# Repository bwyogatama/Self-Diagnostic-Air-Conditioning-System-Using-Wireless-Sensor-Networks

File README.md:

# Self-Diagnostic-Air-Conditioning-System-Using-Wireless-Sensor-Networks

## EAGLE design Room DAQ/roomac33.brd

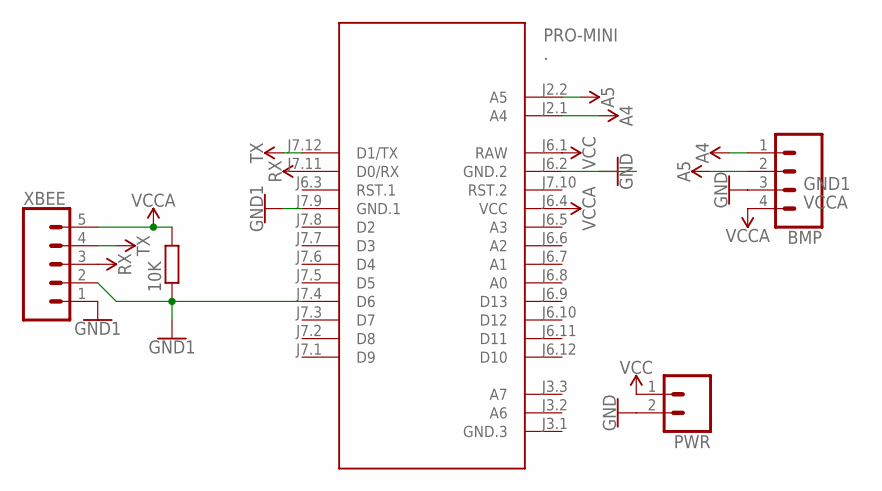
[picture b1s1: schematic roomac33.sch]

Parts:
10K: R0204/7; 0204/7
BMP: CONN_04; 1X04
PRO-MINI: .; ARDUINO-PRO-MINI#NP
PWR: CONN_025MM; SCREWTERMINAL-5MM-2
XBEE: CONN_05; 1X05

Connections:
A4: BMP.1, PRO-MINI.J2.1 (A4)
A5: BMP.2, PRO-MINI.J2.2 (A5)
GND: 10K.1, PRO-MINI.J7.4 (D6), PRO-MINI.J7.9 (GND.1), XBEE.1, XBEE.2
GND1: BMP.3, PRO-MINI.J6.2 (GND.2), PWR.2
RX: PRO-MINI.J7.11 (D0/RX), XBEE.3
TX: PRO-MINI.J7.12 (D1/TX), XBEE.4
VCC: PRO-MINI.J6.1 (RAW), PWR.1
VCCA: 10K.2, BMP.4, PRO-MINI.J6.4 (VCC), XBEE.5

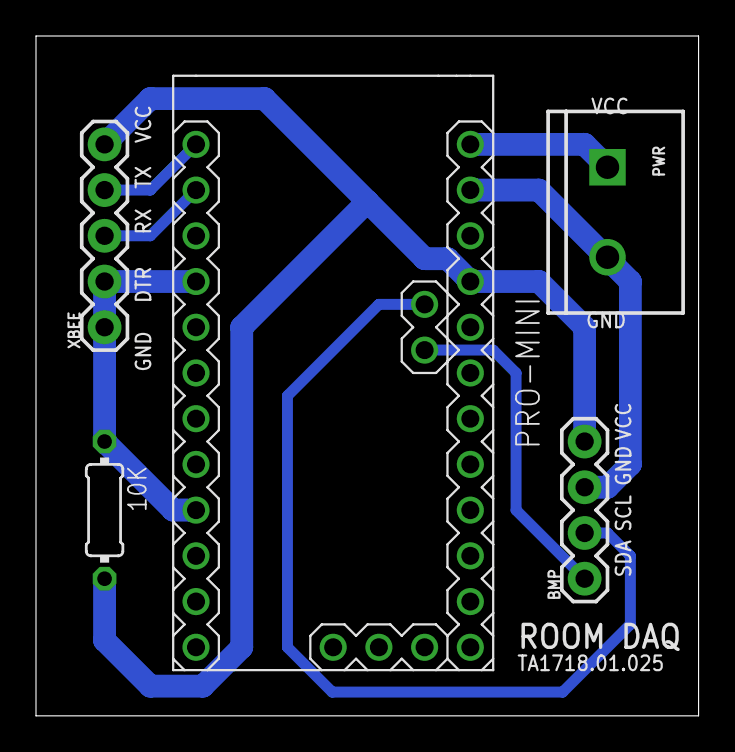
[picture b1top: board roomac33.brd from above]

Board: 2 copper layers, 36.8 x 37.8 mm, 5 parts (0 on the bottom side), 8 nets.

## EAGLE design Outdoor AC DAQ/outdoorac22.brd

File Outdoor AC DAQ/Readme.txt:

Arduino Code for Outdoor AC DAQ

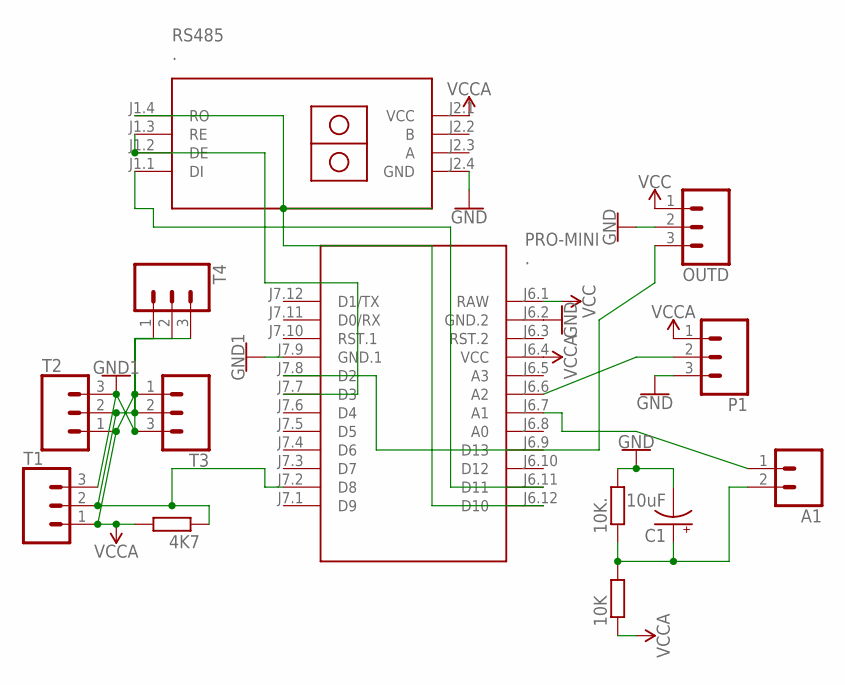
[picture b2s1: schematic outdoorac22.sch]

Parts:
4K7, 10K, 10K.: R0204/7; 0204/7
A1: CONN_02; 1X02
C1: 10uF; CPOL-RADIAL-2.5MM-5MM
OUTD: CONN_03-SCREW-5MM; SCREWTERMINAL-5MM-3
P1: CONN_03; 1X03
PRO-MINI: .; ARDUINO-PRO-MINI#SMP
RS485: .; RS485-TTL-CONVERTER
T1, T2, T3, T4: CONN_03; 1X03

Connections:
GND: PRO-MINI.J7.9 (GND.1), T1.3, T2.3, T3.3, T4.3
GND1: 10K..2, C1.2 (-), OUTD.2, P1.3, PRO-MINI.J6.2 (GND.2), RS485.J2.4 (GND)
unnamed: 4K7.1, PRO-MINI.J7.2 (D8), T1.2, T2.2, T3.2, T4.2
unnamed: A1.1, PRO-MINI.J6.7 (A1)
unnamed: P1.2, PRO-MINI.J6.6 (A2)
unnamed: 10K.2, 10K..1, A1.2, C1.1 (+)
unnamed: PRO-MINI.J7.7 (D3), RS485.J1.2 (DE), RS485.J1.3 (RE)
unnamed: OUTD.3, PRO-MINI.J7.8 (D2)
unnamed: PRO-MINI.J6.11 (D11), RS485.J1.1 (DI)
unnamed: PRO-MINI.J6.12 (D10), RS485.J1.4 (RO)
VCC: OUTD.1, PRO-MINI.J6.1 (RAW)
VCCA: 4K7.2, 10K.1, P1.1, PRO-MINI.J6.4 (VCC), RS485.J2.1 (VCC), T1.1, T2.1, T3.1, T4.1

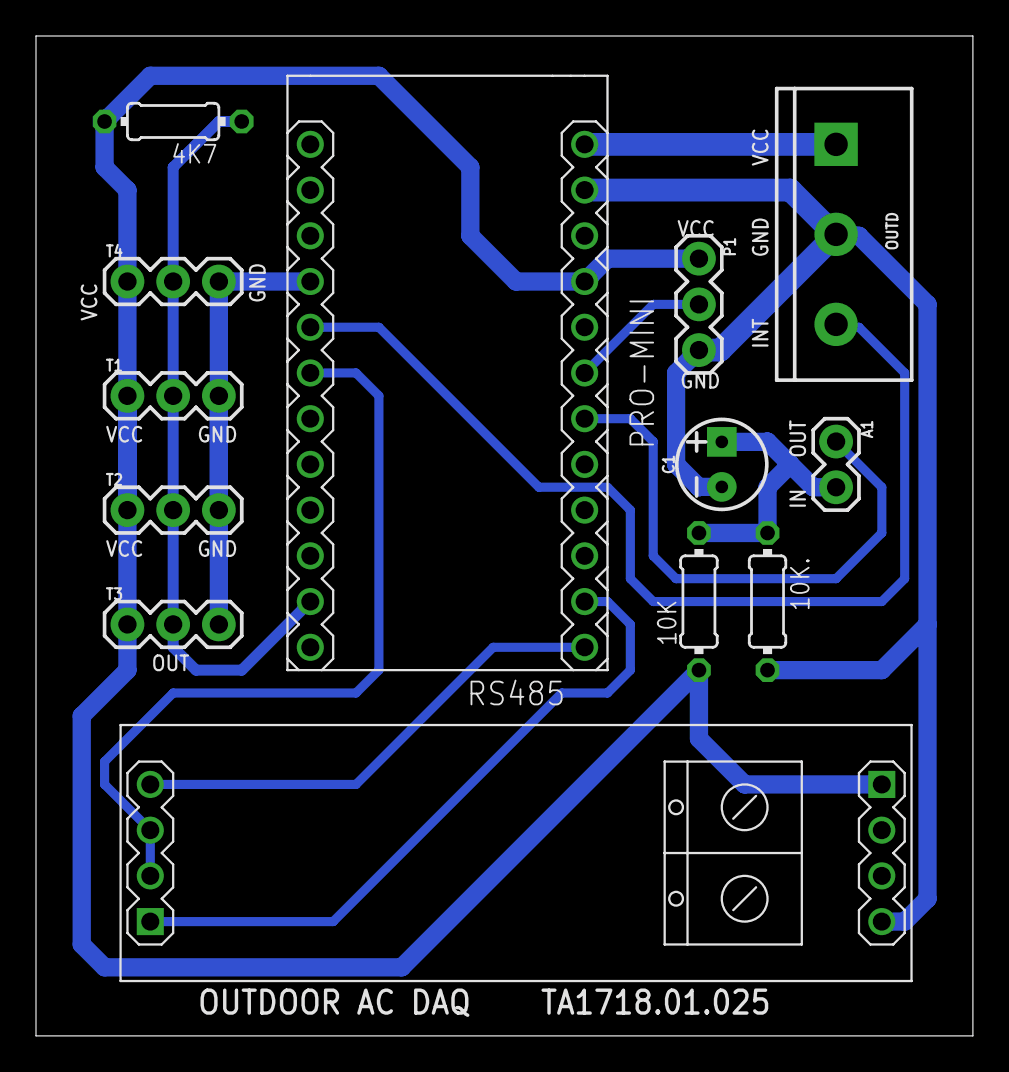
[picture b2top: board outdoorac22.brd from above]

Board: 2 copper layers, 52.0 x 55.5 mm, 13 parts (0 on the bottom side), 12 nets.

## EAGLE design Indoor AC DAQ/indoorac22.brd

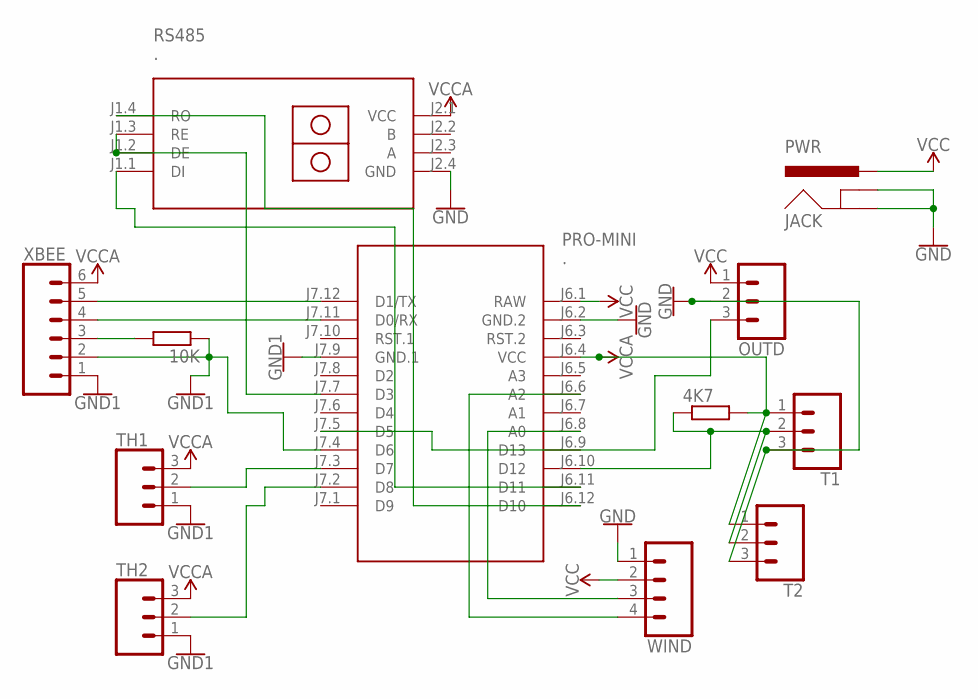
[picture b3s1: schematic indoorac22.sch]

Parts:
4K7, 10K: R0204/7; 0204/7
JACK: PWR; POWER_JACK_PTH_LOCK
OUTD: CONN_03-SCREW-5MM; SCREWTERMINAL-5MM-3
PRO-MINI: .; ARDUINO-PRO-MINI#SMP
RS485: .; RS485-TTL-CONVERTER
T1, T2: CONN_03; 1X03
TH1, TH2: CONN_03; 1X03
WIND: CONN_04; 1X04
XBEE: CONN_06SILK_FEMALE_PTH; 1X06

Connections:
GND: 10K.1, PRO-MINI.J7.4 (D6), PRO-MINI.J7.9 (GND.1), TH1.1, TH2.1, XBEE.1, XBEE.2
GND1: JACK.GND, JACK.GNDBREAK, OUTD.2, PRO-MINI.J6.2 (GND.2), RS485.J2.4 (GND), T1.3, T2.3, WIND.1
unnamed: 4K7.1, PRO-MINI.J6.10 (D12), T1.2, T2.2
unnamed: PRO-MINI.J6.8 (A0), WIND.3
unnamed: 10K.2, XBEE.3
unnamed: PRO-MINI.J6.6 (A2), WIND.4
unnamed: PRO-MINI.J7.7 (D3), RS485.J1.2 (DE), RS485.J1.3 (RE)
unnamed: OUTD.3, PRO-MINI.J7.5 (D5)
unnamed: PRO-MINI.J6.11 (D11), RS485.J1.1 (DI)
unnamed: PRO-MINI.J6.12 (D10), RS485.J1.4 (RO)
unnamed: PRO-MINI.J7.12 (D1/TX), XBEE.5
unnamed: PRO-MINI.J7.11 (D0/RX), XBEE.4
unnamed: PRO-MINI.J7.3 (D7), TH1.2
unnamed: PRO-MINI.J7.2 (D8), TH2.2
VCC: JACK.PWR, OUTD.1, PRO-MINI.J6.1 (RAW), WIND.2
VCCA: 4K7.2, PRO-MINI.J6.4 (VCC), RS485.J2.1 (VCC), T1.1, T2.1, TH1.3, TH2.3, XBEE.6

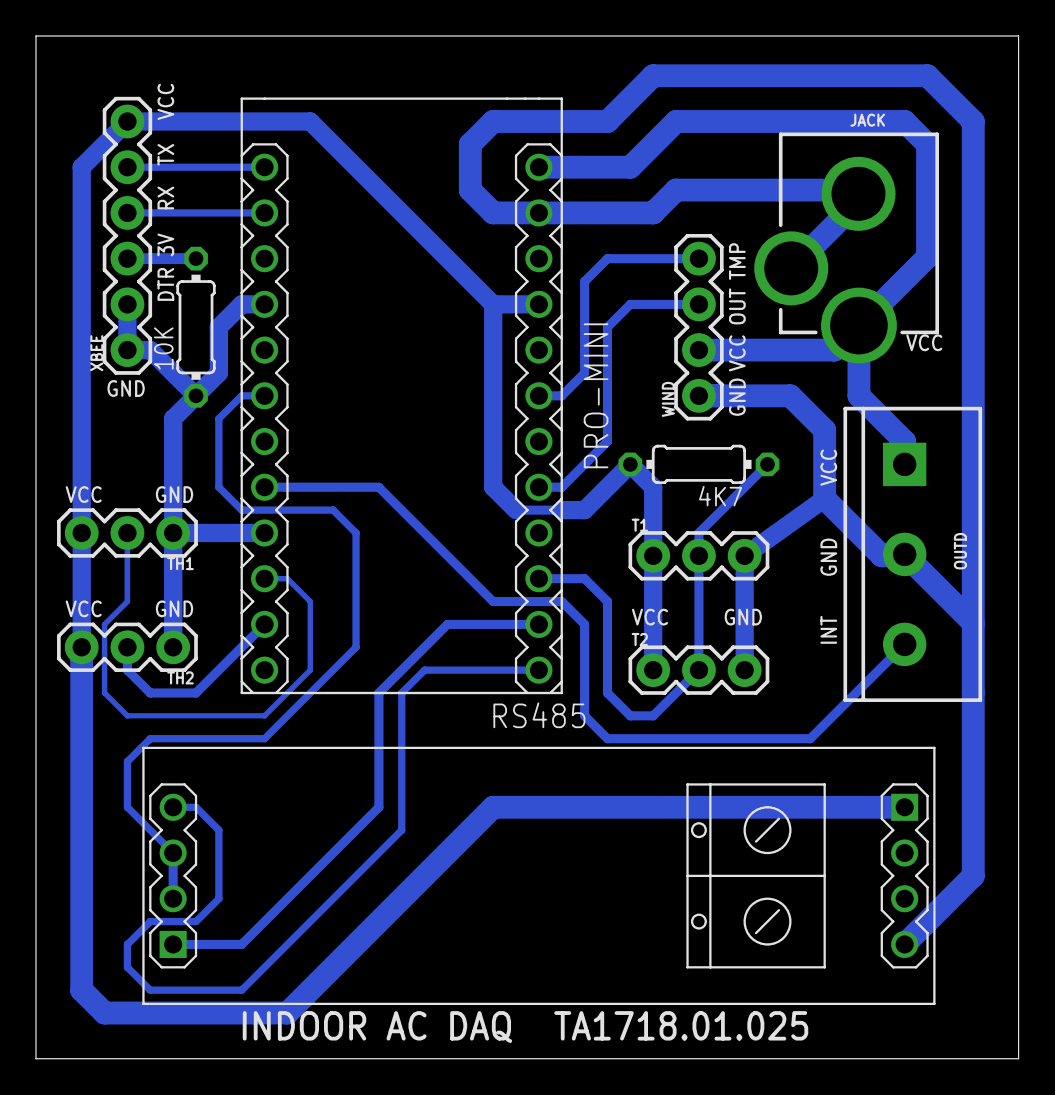
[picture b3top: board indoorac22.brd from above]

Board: 2 copper layers, 54.6 x 56.8 mm, 12 parts (0 on the bottom side), 16 nets.

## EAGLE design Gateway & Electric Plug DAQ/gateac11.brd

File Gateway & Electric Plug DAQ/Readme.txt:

Raspberry Pi Python Code for Gateway
Arduino Code for Electric Plug DAQ

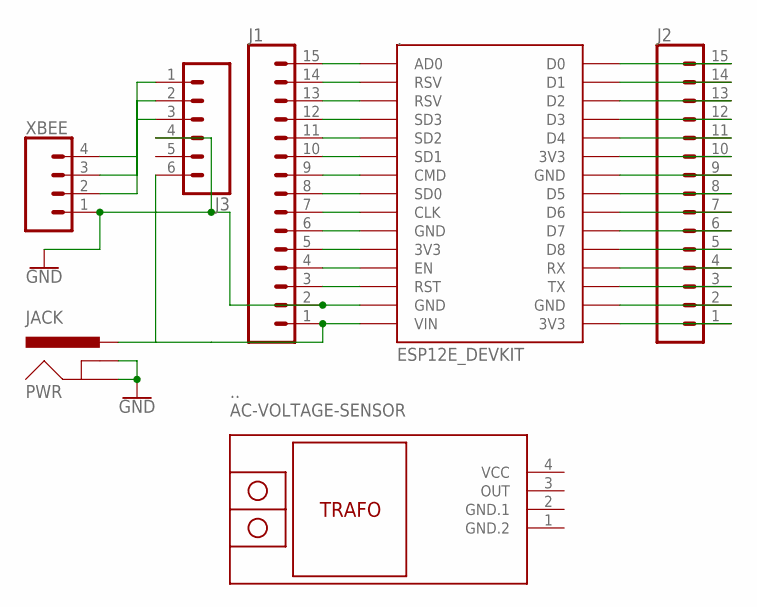
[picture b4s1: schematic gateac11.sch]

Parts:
.: ESP12E_DEVKIT
..: AC-VOLTAGE-SENSOR
J1, J2: CONN_15; 1X15
J3: CONN_06SILK_FEMALE_PTH; 1X06
PWR: JACK; POWER_JACK_PTH_BREAD
XBEE: CONN_04; 1X04

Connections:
3V3: J3.1, XBEE.4
GND: ..GND@1 (GND), J1.2, J3.4, PWR.GND, PWR.GNDBREAK, XBEE.1
GND.1: ...2 (GND.1)
GND.2: ...1 (GND.2)
unnamed: ..AD0, J1.15
unnamed: ..RSV@0 (RSV), J1.14
unnamed: ..RSV@1 (RSV), J1.13
unnamed: ..SD3, J1.12
unnamed: ..SD2, J1.11
unnamed: ..SD1, J1.10
unnamed: ..CMD, J1.9
unnamed: ..SD0, J1.8
unnamed: ..CLK, J1.7
unnamed: ..GND@0 (GND), J1.6
unnamed: ..3V3@0 (3V3), J1.5
unnamed: ..EN, J1.4
unnamed: ..RST, J1.3
unnamed: ..VIN, J1.1, J3.6, PWR.PWR
unnamed: ..D0, J2.15
unnamed: ..D1, J2.14
unnamed: ..D2, J2.13
unnamed: ..D3, J2.12
unnamed: ..D4, J2.11
unnamed: ..3V3@1 (3V3), J2.10
unnamed: ..GND@2 (GND), J2.9
unnamed: ..D5, J2.8
unnamed: ..D6, J2.7
unnamed: ..D7, J2.6
unnamed: ..D8, J2.5
unnamed: ..RX, J2.4
unnamed: ..TX, J2.3
unnamed: ..GND@3 (GND), J2.2
unnamed: ..3V3@2 (3V3), J2.1
RX: J3.3, XBEE.2
TX: J3.2, XBEE.3
VCC: ...4 (VCC)

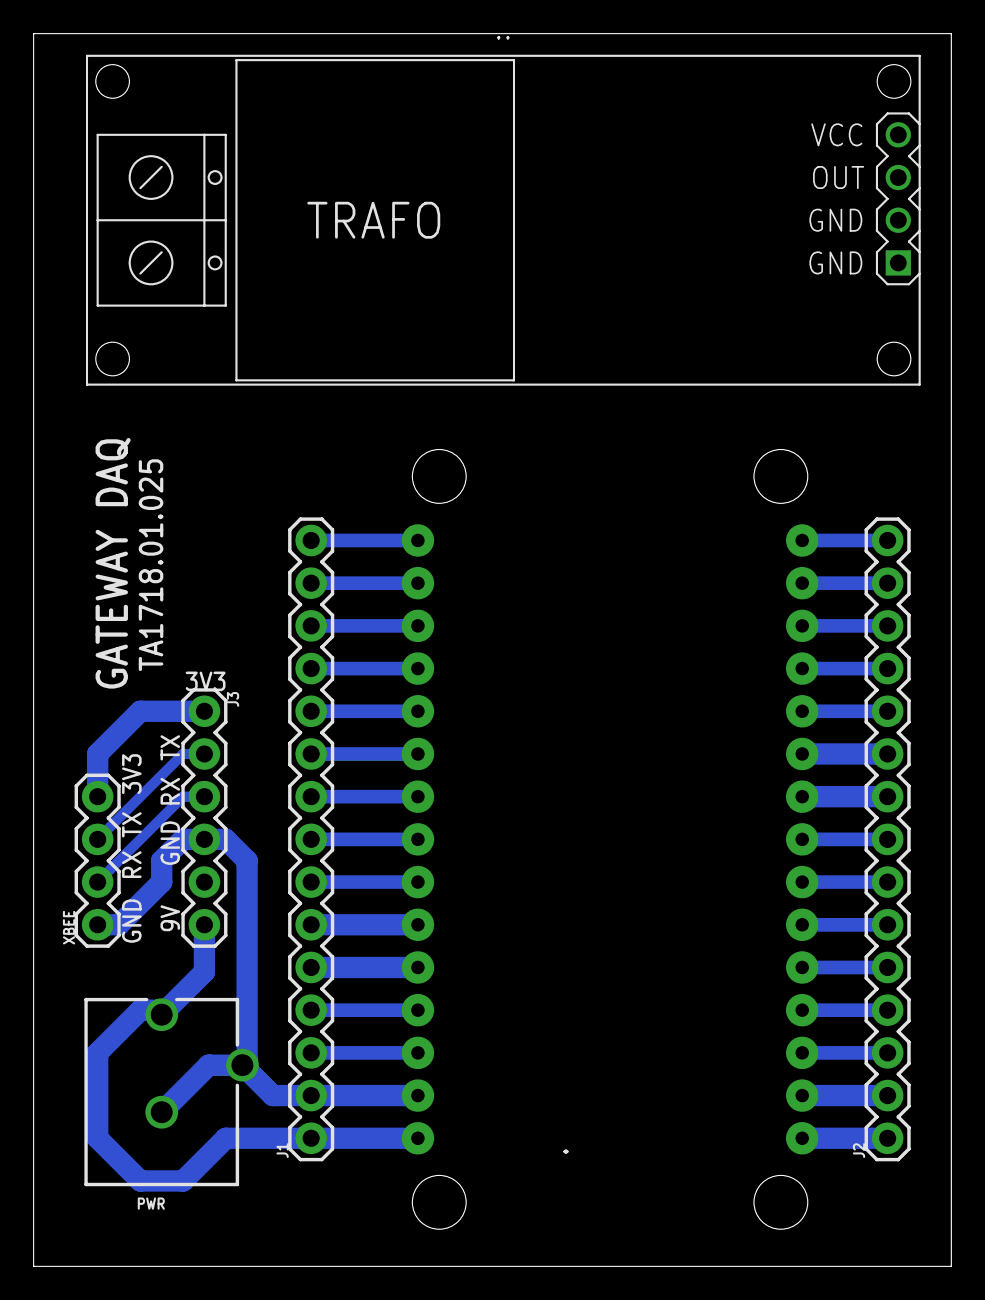
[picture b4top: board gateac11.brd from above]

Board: 2 copper layers, 54.6 x 73.3 mm, 7 parts (0 on the bottom side), 33 nets.

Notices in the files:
parts and their libraries:
SparkFun-Connectors: Licensing: Creative Commons ShareAlike 4.0 International - https://creativecommons.org/licenses/by-sa/4.0
diy-modules: Released under the Creative Commons Attribution 4.0 International License: http://creativecommons.org/licenses/by/4.0
